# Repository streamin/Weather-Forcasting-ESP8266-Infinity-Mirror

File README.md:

# Weather Forcasting ESP8266 Infinity Mirror
A WiFi connected Infinity Mirror that displays current and forecasted weather information with NeoPixels. Writen with the Arduino IDE.

The infinity mirror has an arbitrary number of panes.
Each pane has an equal but arbitrary number of NeoPixels.
Each pane represents the current weather or the weather for a specified forecast period.
Weather data is from the Dark Sky API (https://darksky.net/dev/docs).

Temperature is represented by the hue of the NeoPixels.
Wind Angle is represented by a single NeoPixel whose position on the perimeter of the pane coresponds to the Wind Angle.
Wind Speed is represented by the saturation of the Wind Angle NeoPixel.
Probability of Percipitation is represented by a twinkling effect.

As the weather forecast is updated there are smooth transitions in the appearence of the NeoPixels. Temperature is relative to the seasonal averages so the hue changes frequently. Without this feature the NeoPixel hues would only change with the season.

Uses ArduionJson (https://github.com/bblanchon/ArduinoJson) and NeoPixelBus (https://github.com/Makuna/NeoPixelBus).

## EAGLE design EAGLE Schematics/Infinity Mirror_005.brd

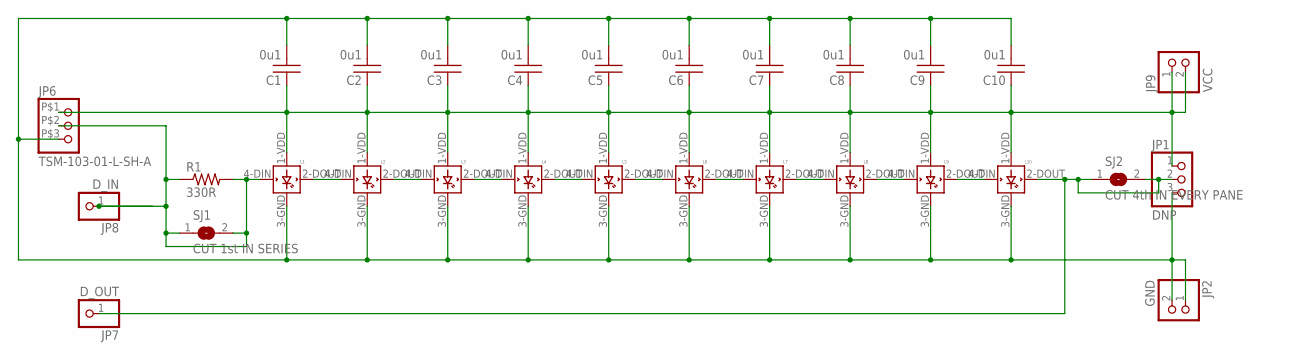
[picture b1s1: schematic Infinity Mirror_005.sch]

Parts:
C1, C2, C3, C4, C5, C6, C7, C8, C9, C10: 0u1; C1206
JP1: DNP; 1X03-CLEANBIG
JP2: GND; 1X02-CLEANBIG
JP6: TSM-103-01-L-SH-A
JP7: D_OUT; 1X01-CLEANBIG
JP8: D_IN; 1X01-CLEANBIG
JP9: VCC; 1X02-CLEANBIG
L1, L2, L3, L4, L5, L6, L7, L8, L9, L10: WS2812B
R1: 330R; R1206
SJ1: CUT 1st IN SERIES; SJ
SJ2: CUT 4th IN EVERY PANE; SJ

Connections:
GND: C1.2, C2.2, C3.2, C4.2, C5.2, C6.2, C7.2, C8.2, C9.2, C10.2, JP1.3, JP2.1, JP2.2, JP6.P$3 (3), L1.3-GND (GND), L2.3-GND (GND), L3.3-GND (GND), L4.3-GND (GND), L5.3-GND (GND), L6.3-GND (GND), L7.3-GND (GND), L8.3-GND (GND), L9.3-GND (GND), L10.3-GND (GND)
unnamed: L2.2-DOUT (DOUT), L3.4-DIN (DIN)
unnamed: L3.2-DOUT (DOUT), L4.4-DIN (DIN)
unnamed: L4.2-DOUT (DOUT), L5.4-DIN (DIN)
unnamed: L5.2-DOUT (DOUT), L6.4-DIN (DIN)
unnamed: L6.2-DOUT (DOUT), L7.4-DIN (DIN)
unnamed: L1.2-DOUT (DOUT), L2.4-DIN (DIN)
unnamed: L7.2-DOUT (DOUT), L8.4-DIN (DIN)
unnamed: L8.2-DOUT (DOUT), L9.4-DIN (DIN)
unnamed: JP6.P$2 (2), JP8.1, L1.4-DIN (DIN), R1.1, R1.2, SJ1.1, SJ1.2
unnamed: L9.2-DOUT (DOUT), L10.4-DIN (DIN)
unnamed: JP1.2, JP7.1, L10.2-DOUT (DOUT), SJ2.1, SJ2.2
VCC: C1.1, C2.1, C3.1, C4.1, C5.1, C6.1, C7.1, C8.1, C9.1, C10.1, JP1.1, JP6.P$1 (1), JP9.1, JP9.2, L1.1-VDD (VDD), L2.1-VDD (VDD), L3.1-VDD (VDD), L4.1-VDD (VDD), L5.1-VDD (VDD), L6.1-VDD (VDD), L7.1-VDD (VDD), L8.1-VDD (VDD), L9.1-VDD (VDD), L10.1-VDD (VDD)

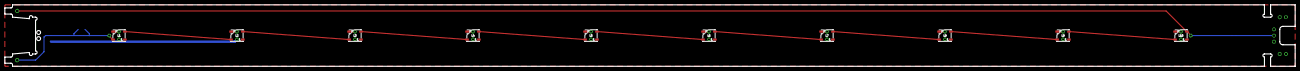
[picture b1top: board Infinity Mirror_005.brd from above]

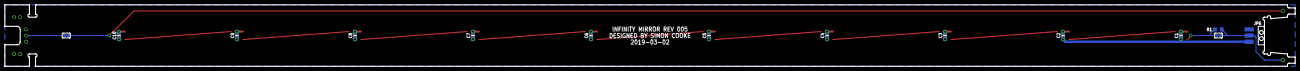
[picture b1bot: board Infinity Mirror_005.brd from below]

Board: 2 copper layers, 533.4 x 25.4 mm, 29 parts (14 on the bottom side), 13 nets.

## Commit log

2018-09-06 Rename CONSTANTS - Copy.h to CONSTANTS.h
2018-09-06 Create empty
2018-09-07 Update and rename empty to about schematics
2018-09-07 Update and rename schematics/about schematics to EAGLE Schematics/About
2018-09-07 Rename schematics/Infinity Mirror_002.brd to EAGLE Schematics/Infinity Mirror_002.brd
2018-09-07 Rename schematics/Infinity Mirror_002.sch to EAGLE Schematics/Infinity Mirror_002.sch
2018-09-07 Update INFINITY_MIRROR.ino
    Added "% 360" to line 402
2018-09-07 Create LICENSE
2019-03-02 Add files via upload
    LED PCB strip for 20"x20" infinity mirror pane. Socket for glass and PCB assembly should be 21"x21".
